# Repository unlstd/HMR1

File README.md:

> This repo documents my progress in creating my first fully functional 16-bit computer. At first, it wasn't even supposed to be public. I made it public mainly to make it easier to work on the project across different devices and to get quicker help from my friends. Because of that, please consider this project more as a documentation of someone's progress rather than a fully documented architecture.

With that being said, I can now introduce you to the project and what I'm trying to achieve.

HMR1 is a 16-bit, non-pipelined computer running at 4 MHz with 8 GPRs.

It contains the following components:

* ALU with two 16-bit special registers for latching operands
* MAR
* MDR
* SP
* HP
* IR
* 8 × 16-bit GPRs
* FR
* PC (also known as IP)
* Internal 4 MHz clock and reset signal generator
* CU
* IC (Interrupt Controller)

The computer itself is still a work in progress, but most of it is already done.

You can track the progress using the checklist below:

* [x] ALU
* [x] MAR
* [x] MDR
* [x] SP
* [x] HP
* [x] GPRs
* [x] FR
* [x] PC
* [x] IR
* [x] IC
* [x] CU
* [x] Motherboard
* [x] Internal 4 MHz clock and reset signal generator

So, even though all the schematics are complete, that doesn't mean the PCBs have been made yet. Here's a little checklist to track the progress of designing the actual PCBs:

* [ ] ALU
* [ ] MAR
* [ ] MDR
* [ ] SP
* [ ] HP
* [ ] GPRs
* [ ] FR
* [ ] PC
* [ ] IR
* [ ] IC
* [ ] CU
* [ ] Motherboard
* [ ] Internal 4 MHz clock and reset signal generator

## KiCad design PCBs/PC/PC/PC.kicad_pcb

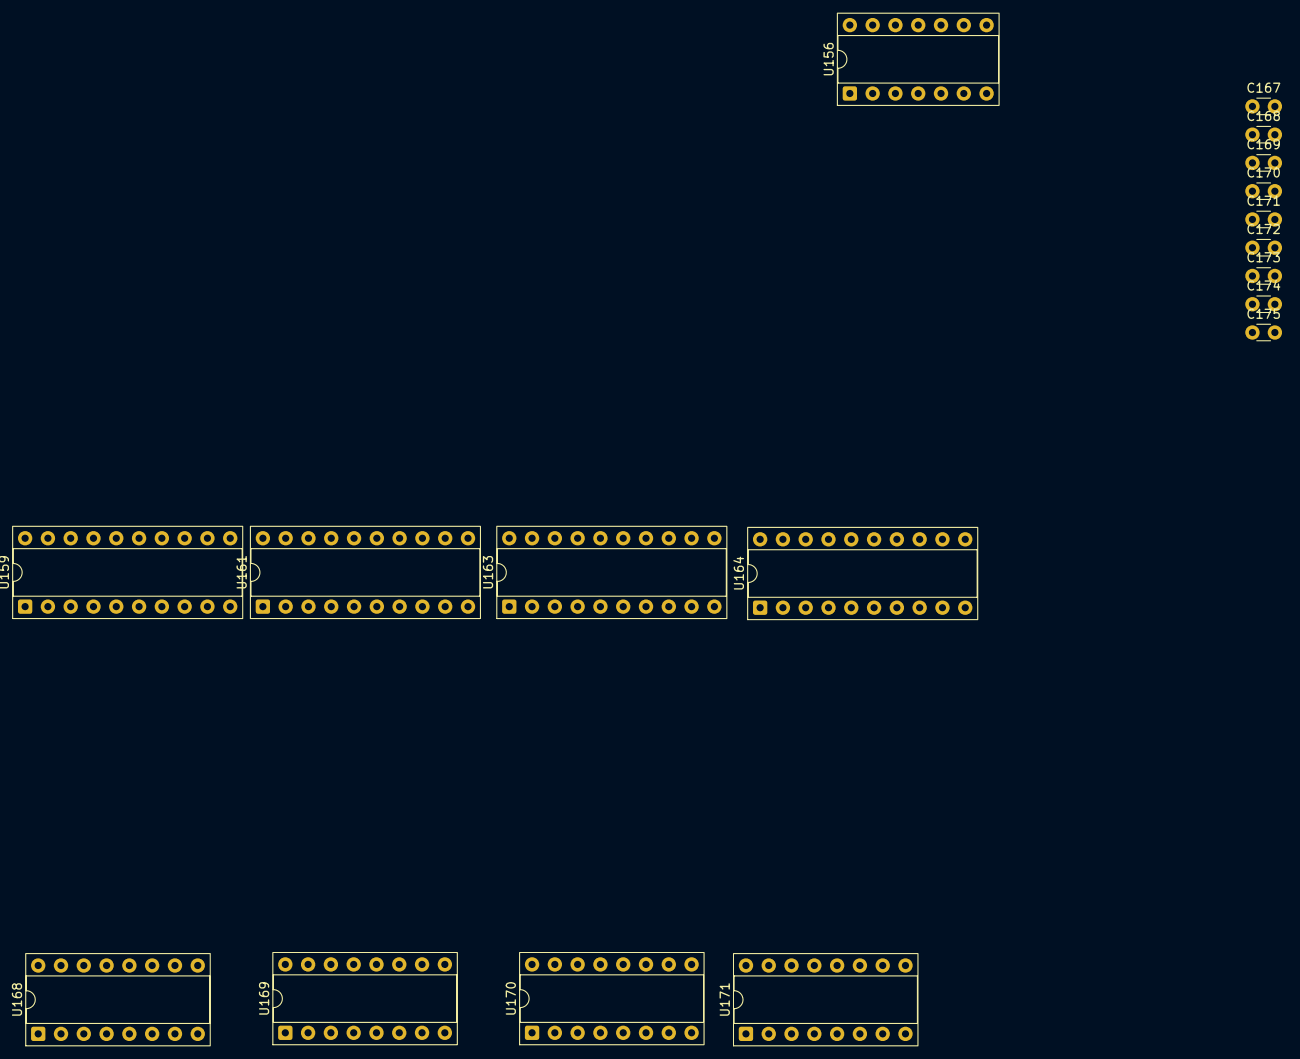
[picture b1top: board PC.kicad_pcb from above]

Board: 2 copper layers, 18 parts (0 on the bottom side), 44 nets, no tracks yet.

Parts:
C167, C168, C169, C170, C171, C172, C173, C174, C175: 100nF; C_Disc_D3.0mm_W1.6mm_P2.50mm
U156: 74HC04; DIP-14_W7.62mm_Socket
U159, U161, U163, U164: 74HC245; DIP-20_W7.62mm_Socket
U168, U169, U170, U171: 74LS161; DIP-16_W7.62mm_Socket

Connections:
+5V: C167.1, C170.1, C171.1, C173.1, U159.1 (A->B), U159.20 (VCC), U161.1 (A->B), U161.20 (VCC), U163.1 (A->B), U163.20 (VCC), U164.1 (A->B), U164.20 (VCC)
/#PC_DATA_IN: U168.9 (~PE), U169.9 (~PE), U170.9 (~PE), U171.9 (~PE)
/#PC_DATA_OUT: U159.19 (CE), U161.19 (CE)
/#RESET: U168.1 (~MR), U169.1 (~MR), U170.1 (~MR), U171.1 (~MR)
/CLK: U168.2 (CP), U169.2 (CP), U170.2 (CP), U171.2 (CP)
/D0: U159.18 (B0), U168.3 (D0)
/D1: U159.17 (B1), U168.4 (D1)
/D2: U159.16 (B2), U168.5 (D2)
/D3: U159.15 (B3), U168.6 (D3)
/D4: U159.14 (B4), U169.3 (D0)
/D5: U159.13 (B5), U169.4 (D1)
/D6: U159.12 (B6), U169.5 (D2)
/D7: U159.11 (B7), U169.6 (D3)
/D8: U161.18 (B0), U170.3 (D0)
/D9: U161.17 (B1), U170.4 (D1)
/D10: U161.16 (B2), U170.5 (D2)
/D11: U161.15 (B3), U170.6 (D3)
/D12: U161.14 (B4), U171.3 (D0)
/D13: U161.13 (B5), U171.4 (D1)
/D14: U161.12 (B6), U171.5 (D2)
/D15: U161.11 (B7), U171.6 (D3)
/PC_ADDR_OUT#: U163.19 (CE), U164.19 (CE)
/Vcc: C168.1, C169.1, C172.1, C174.1, C175.1, U156.14 (VCC), U168.16 (VCC), U169.16 (VCC), U170.16 (VCC), U171.16 (VCC)
GND: C167.2, C168.2, C169.2, C170.2, C171.2, C172.2, C173.2, C174.2, C175.2, U156.7 (GND), U159.10 (GND), U161.10 (GND), U163.10 (GND), U164.10 (GND), U168.8 (GND), U169.8 (GND), U170.8 (GND), U171.8 (GND)
unnamed: U159.2 (A0), U163.2 (A0), U168.14 (Q0)
unnamed: U159.3 (A1), U163.3 (A1), U168.13 (Q1)
unnamed: U159.4 (A2), U163.4 (A2), U168.12 (Q2)
unnamed: U159.5 (A3), U163.5 (A3), U168.11 (Q3)
unnamed: U159.6 (A4), U163.6 (A4), U169.14 (Q0)
unnamed: U159.7 (A5), U163.7 (A5), U169.13 (Q1)
unnamed: U159.8 (A6), U163.8 (A6), U169.12 (Q2)
unnamed: U159.9 (A7), U163.9 (A7), U169.11 (Q3)
unnamed: U161.2 (A0), U164.2 (A0), U170.14 (Q0)
unnamed: U161.3 (A1), U164.3 (A1), U170.13 (Q1)
unnamed: U161.4 (A2), U164.4 (A2), U170.12 (Q2)
unnamed: U161.5 (A3), U164.5 (A3), U170.11 (Q3)
unnamed: U161.6 (A4), U164.6 (A4), U171.14 (Q0)
unnamed: U161.7 (A5), U164.7 (A5), U171.13 (Q1)
unnamed: U161.8 (A6), U164.8 (A6), U171.12 (Q2)
unnamed: U161.9 (A7), U164.9 (A7), U171.11 (Q3)
unnamed: U156.2, U168.7 (CEP), U168.10 (CET), U169.7 (CEP), U170.7 (CEP), U171.7 (CEP)
unnamed: U168.15 (TC), U169.10 (CET)
unnamed: U169.15 (TC), U170.10 (CET)
unnamed: U170.15 (TC), U171.10 (CET)
